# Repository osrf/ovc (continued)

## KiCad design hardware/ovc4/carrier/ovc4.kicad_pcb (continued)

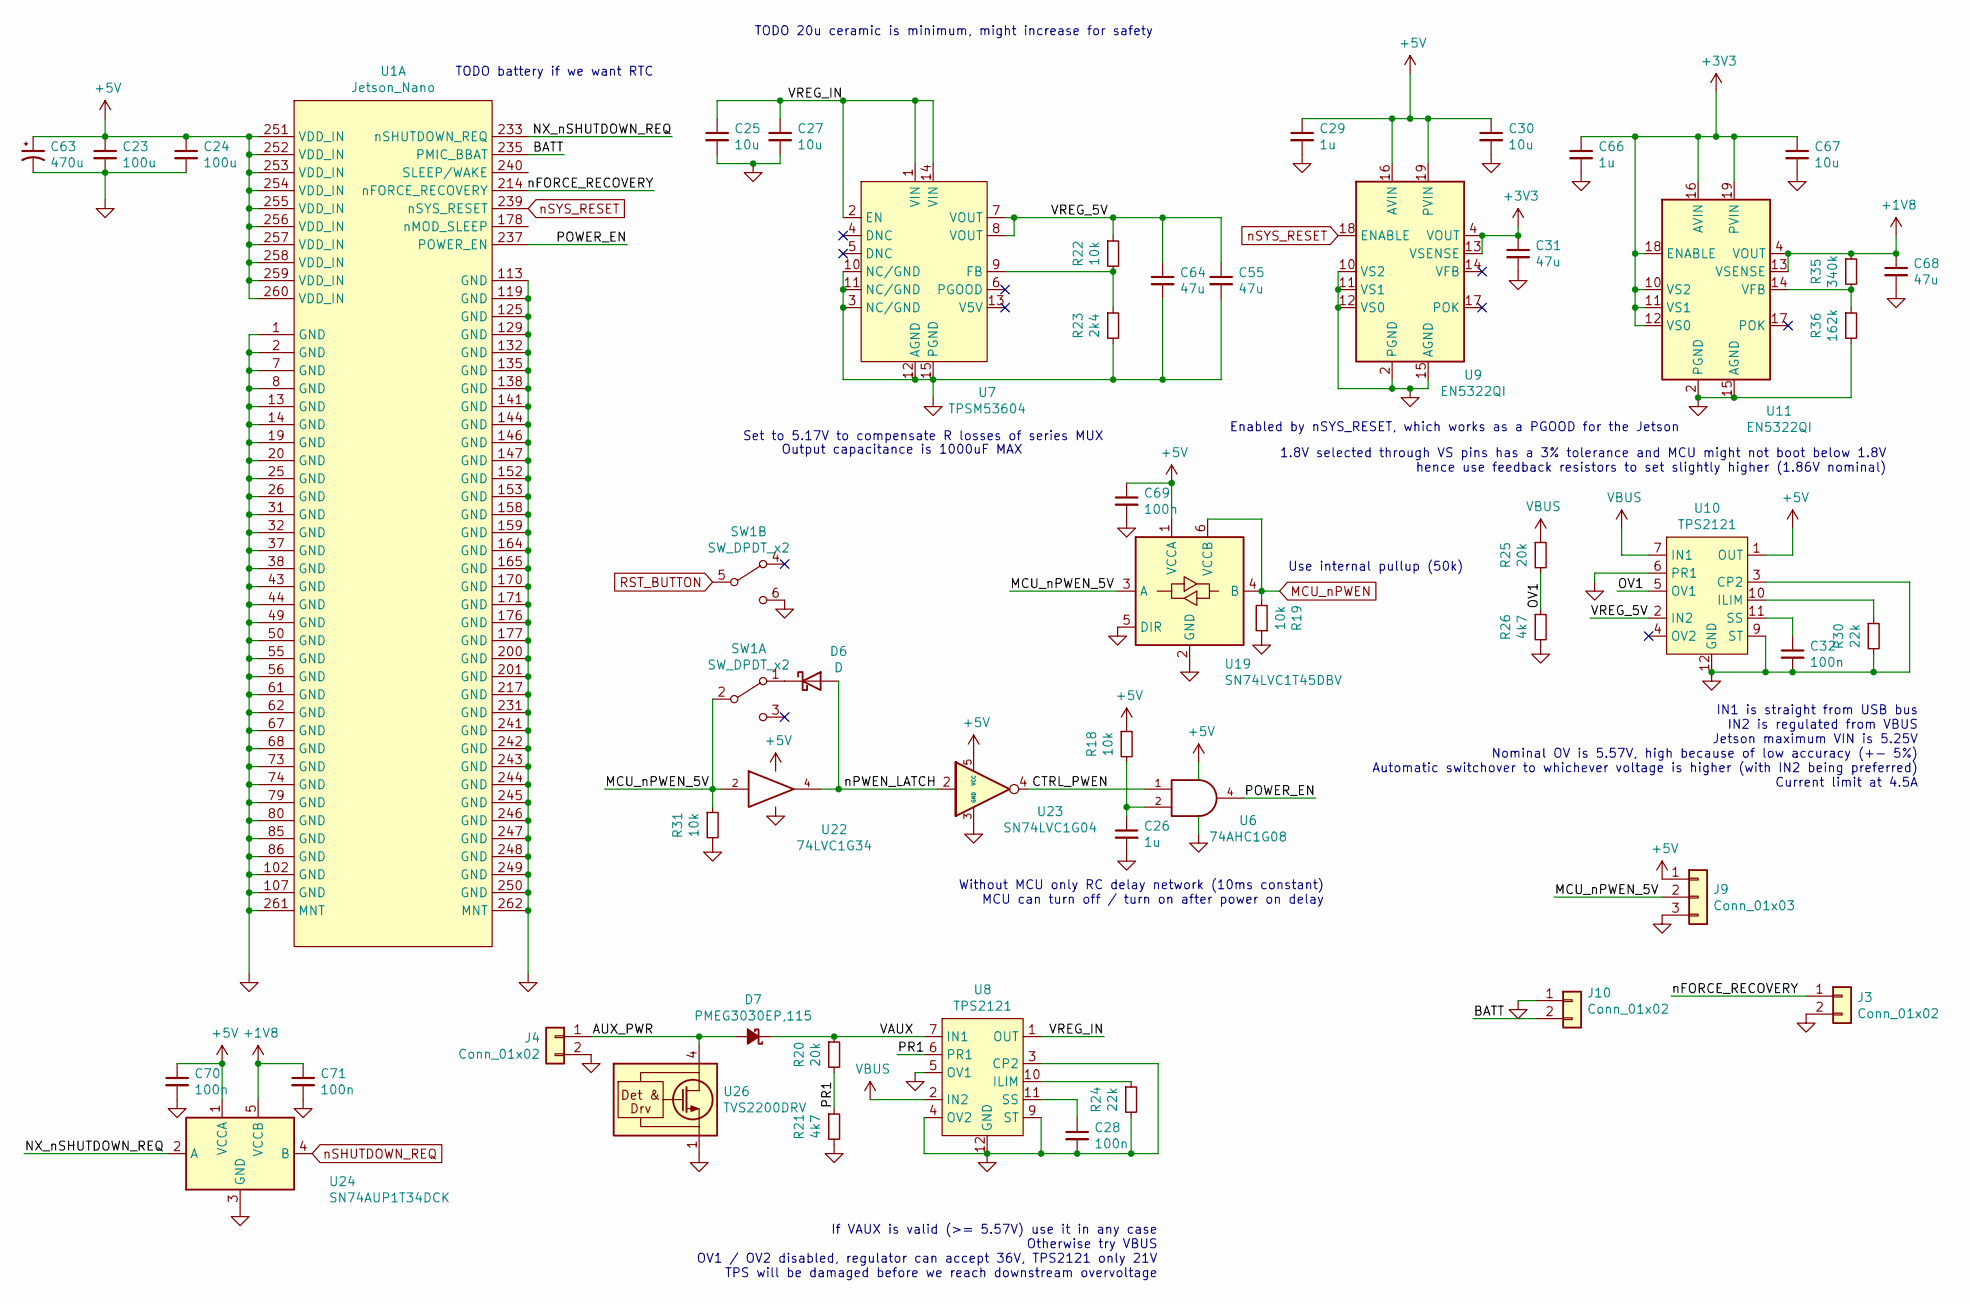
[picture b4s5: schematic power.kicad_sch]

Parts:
C23, C24: 100u; C_1206_3216Metric; MPN C3216X5R1A107M160AC
C25, C27: 10u; C_1206_3216Metric; MPN C1206C106M3PACTU
C26, C29, C66: 1u; C_0402_1005Metric; MPN CL05A105KA5NQNC
C28, C32, C69, C70, C71: 100n; C_0402_1005Metric; MPN CL05F104ZO5NNNC
C30, C67: 10u; C_0805_2012Metric; MPN C0805C106K8PACTU
C31, C55, C64, C68: 47u; C_1206_3216Metric; MPN GRM31CR61A476KE15L
C63: 470u; CP_Elec_6.3x7.7; MPN EEE-FTJ471XAP
D6: D; D_0402_1005Metric; MPN CDBQR0130L
D7: PMEG3030EP,115; D_SOD-128; MPN PMEG3030EP,115
J3: Conn_01x02; PinHeader_1x02_P2.54mm_Vertical; MPN 952-2262-ND
J4: Conn_01x02; Molex_Nano-Fit_105313-xx02_1x02_P2.50mm_Horizontal; MPN 1053131302
J9: Conn_01x03; PinHeader_1x03_P2.54mm_Vertical; MPN CONN HEADER VERT 3POS 2.54MM
J10: Conn_01x02; ELNA_DSK-3R3H224U-HL; MPN DSK-3R3H224U-HL
R18, R19, R22, R31: 10k; R_0402_1005Metric; MPN ERA-2AED103X
R20, R25: 20k; R_0402_1005Metric; MPN ERA-2AED103X
R21, R26: 4k7; R_0402_1005Metric; MPN ERJ-2RKF4701X
R23: 2k4; R_0402_1005Metric; MPN ERA-2AED242X
R24, R30: 22k; R_0402_1005Metric; MPN ERJ-2RKF2202X
R35: 340k; R_0402_1005Metric; MPN ERJ-2RKF3403X
R36: 162k; R_0402_1005Metric; MPN ERJ-2RKF1623X
SW1: SW_DPDT_x2; TL2230; MPN TL2230OAF140
U1: Jetson_Nano; TE_2309413-1; MPN 2309413-1
U6: 74AHC1G08; SOT-353_SC-70-5; MPN SN74AHC1G08DCKR
U7: TPSM53604; TI_B3QFN; MPN TPSM53604RDAR
U8, U10: TPS2121; Texas_VQFN-HR-12_2x2.5_Pitch0.5mm; MPN TPS2121RUXR
U9, U11: EN5322QI; Converter_DCDC_Intel_QFN-24_4x6mm_P0.65mm_ThermalVias; MPN EN5322QI
U19: SN74LVC1T45DBV; SOT-23-6; MPN SN74LVC1T45DBVR
U22: 74LVC1G34; SOT-23-5; MPN SN74LVC1G34DBVR
U23: SN74LVC1G04; SOT-353_SC-70-5; MPN SN74LVC1G04DCKR
U24: SN74AUP1T34DCK; SOT-353_SC-70-5; MPN SN74AUP1T34DCKR
U26: TVS2200DRV; WSON-6-1EP_2x2mm_P0.65mm_EP1x1.6mm; MPN TVS2200DRVR

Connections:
+1V8: C68.1, C71.1, R35.1, U11.4 (VOUT), U11.5 (VOUT), U11.6 (VOUT), U11.7 (VOUT), U11.13 (VSENSE), U24.5 (VCCB); also elsewhere on the board
+5V: C23.1, C24.1, C29.1, C30.1, C63.1, C69.1, C70.1, J9.1, R18.1, U1.251 (VDD_IN), U1.252 (VDD_IN), U1.253 (VDD_IN), U1.254 (VDD_IN), U1.255 (VDD_IN), U1.256 (VDD_IN), U1.257 (VDD_IN), U1.258 (VDD_IN), U1.259 (VDD_IN), U1.260 (VDD_IN), U6.5 (VCC), U9.16 (AVIN), U9.19 (PVIN), U9.20 (PVIN), U10.1 (OUT), U10.8 (OUT), U19.1 (VCCA), U22.5 (VCC), U23.5 (VCC), U24.1 (VCCA); also elsewhere on the board
/Power/AUX_PWR: D7.2 (A), J4.1, U26.4 (IN), U26.5 (IN), U26.6 (IN)
/Power/BATT: J10.2, U1.235 (PMIC_BBAT)
/Power/CTRL_PWEN: U6.1, U23.4
/Power/MCU_nPWEN_5V: J9.2, R31.1, SW1.2 (B), U19.3 (A), U22.2
/Power/NX_nSHUTDOWN_REQ: U1.233 (nSHUTDOWN_REQ), U24.2 (A)
/Power/OV1: R25.2, R26.1, U10.5 (OV1)
/Power/POWER_EN: U1.237 (POWER_EN), U6.4
/Power/PR1: R20.2, R21.1, U8.6 (PR1)
/Power/VAUX: D7.1 (K), R20.1, U8.7 (IN1)
/Power/VREG_5V: C55.1, C64.1, R22.1, U7.7 (VOUT), U7.8 (VOUT), U10.2 (IN2)
/Power/VREG_IN: C25.1, C27.1, U7.1 (VIN), U7.2 (EN), U7.14 (VIN), U8.1 (OUT), U8.8 (OUT)
/Power/nFORCE_RECOVERY: J3.1, U1.214 (nFORCE_RECOVERY)
/Power/nPWEN_LATCH: D6.2 (A), U22.4, U23.2
GND: C23.2, C24.2, C25.2, C26.2, C27.2, C28.2, C29.2, C30.2, C31.2, C32.2, C55.2, C63.2, C64.2, C66.2, C67.2, C68.2, C69.2, C70.2, C71.2, J3.2, J4.2, J9.3, J10.1, R19.1, R21.2, R23.2, R24.2, R26.2, R30.2, R31.2, R36.2, SW1.6 (C), U1.1 (GND), U1.2 (GND), U1.7 (GND), U1.8 (GND), U1.13 (GND), U1.14 (GND), U1.19 (GND), U1.20 (GND), U1.25 (GND), U1.26 (GND), U1.31 (GND), U1.32 (GND), U1.37 (GND), U1.38 (GND), U1.43 (GND), U1.44 (GND), U1.49 (GND), U1.50 (GND), U1.55 (GND), U1.56 (GND), U1.61 (GND), U1.62 (GND), U1.67 (GND), U1.68 (GND), U1.73 (GND), U1.74 (GND), U1.79 (GND), U1.80 (GND), U1.85 (GND), U1.86 (GND), U1.102 (GND), U1.107 (GND), U1.113 (GND), U1.119 (GND), U1.125 (GND), U1.129 (GND), U1.132 (GND), U1.135 (GND), U1.138 (GND), U1.141 (GND), U1.144 (GND), U1.146 (GND), U1.147 (GND), U1.152 (GND), U1.153 (GND), U1.158 (GND), U1.159 (GND), U1.164 (GND), U1.165 (GND), U1.170 (GND), U1.171 (GND), U1.176 (GND), U1.177 (GND), U1.200 (GND), U1.201 (GND), U1.217 (GND), U1.231 (GND), U1.241 (GND), U1.242 (GND), U1.243 (GND), U1.244 (GND), U1.245 (GND), U1.246 (GND), U1.247 (GND), U1.248 (GND), U1.249 (GND), U1.250 (GND), U1.261 (MNT), U1.262 (MNT), U6.3 (GND), U7.3 (NC/GND), U7.10 (NC/GND), U7.11 (NC/GND), U7.12 (AGND), U7.15 (PGND), U8.3 (CP2), U8.4 (OV2), U8.5 (OV1), U8.9 (ST), U8.12 (GND), U9.2 (PGND), U9.3 (PGND), U9.8 (PGND), U9.9 (PGND), U9.10 (VS2), U9.11 (VS1), U9.12 (VS0), U9.15 (AGND), U9.25 (PGND), U10.3 (CP2), U10.6 (PR1), U10.9 (ST), U10.12 (GND), U11.2 (PGND), U11.3 (PGND), U11.8 (PGND), U11.9 (PGND), U11.15 (AGND), U11.25 (PGND), U19.2 (GND), U19.5 (DIR), U22.3 (GND), U23.3 (GND), U24.3 (GND), U26.1 (GND), U26.2 (GND), U26.3 (GND), U26.7 (GND); also elsewhere on the board
MCU_nPWEN: R19.2, U19.4 (B), U19.6 (VCCB); also elsewhere on the board
unnamed: C26.1, R18.2, U6.2
unnamed: C28.1, U8.11 (SS)
unnamed: C32.1, U10.11 (SS)
unnamed: D6.1 (K), SW1.1 (A)
unnamed: R22.2, R23.1, U7.9 (FB)
unnamed: R24.1, U8.10 (ILIM)
unnamed: R30.1, U10.10 (ILIM)
unnamed: R35.2, R36.1, U11.14 (VFB)
RST_BUTTON: SW1.5 (B); also elsewhere on the board
VBUS: R25.1, U8.2 (IN2), U10.7 (IN1); also elsewhere on the board
nSHUTDOWN_REQ: U24.4 (B); also elsewhere on the board
nSYS_RESET: U1.239 (nSYS_RESET), U9.18 (ENABLE); also elsewhere on the board

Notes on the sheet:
TODO battery if we want RTC
Output capacitance is 1000uF MAX
Set to 5.17V to compensate R losses of series MUX
TODO 20u ceramic is minimum, might increase for safety
If VAUX is valid (>= 5.57V) use it in any case Otherwise try VBUS OV1 / OV2 disabled, regulator can accept 36V, TPS2121 only 21V TPS will be damaged before we reach downstream overvoltage
Without MCU only RC delay network (10ms constant) MCU can turn off / turn on after power on delay
Use internal pullup (50k)
Enabled by nSYS_RESET, which works as a PGOOD for the Jetson
1.8V selected through VS pins has a 3% tolerance and MCU might not boot below 1.8V hence use feedback resistors to set slightly higher (1.86V nominal)
IN1 is straight from USB bus IN2 is regulated from VBUS Jetson maximum VIN is 5.25V Nominal OV is 5.57V, high because of low accuracy (+- 5%) Automatic switchover to whichever voltage is higher (with IN2 being preferred) Current limit at 4.5A

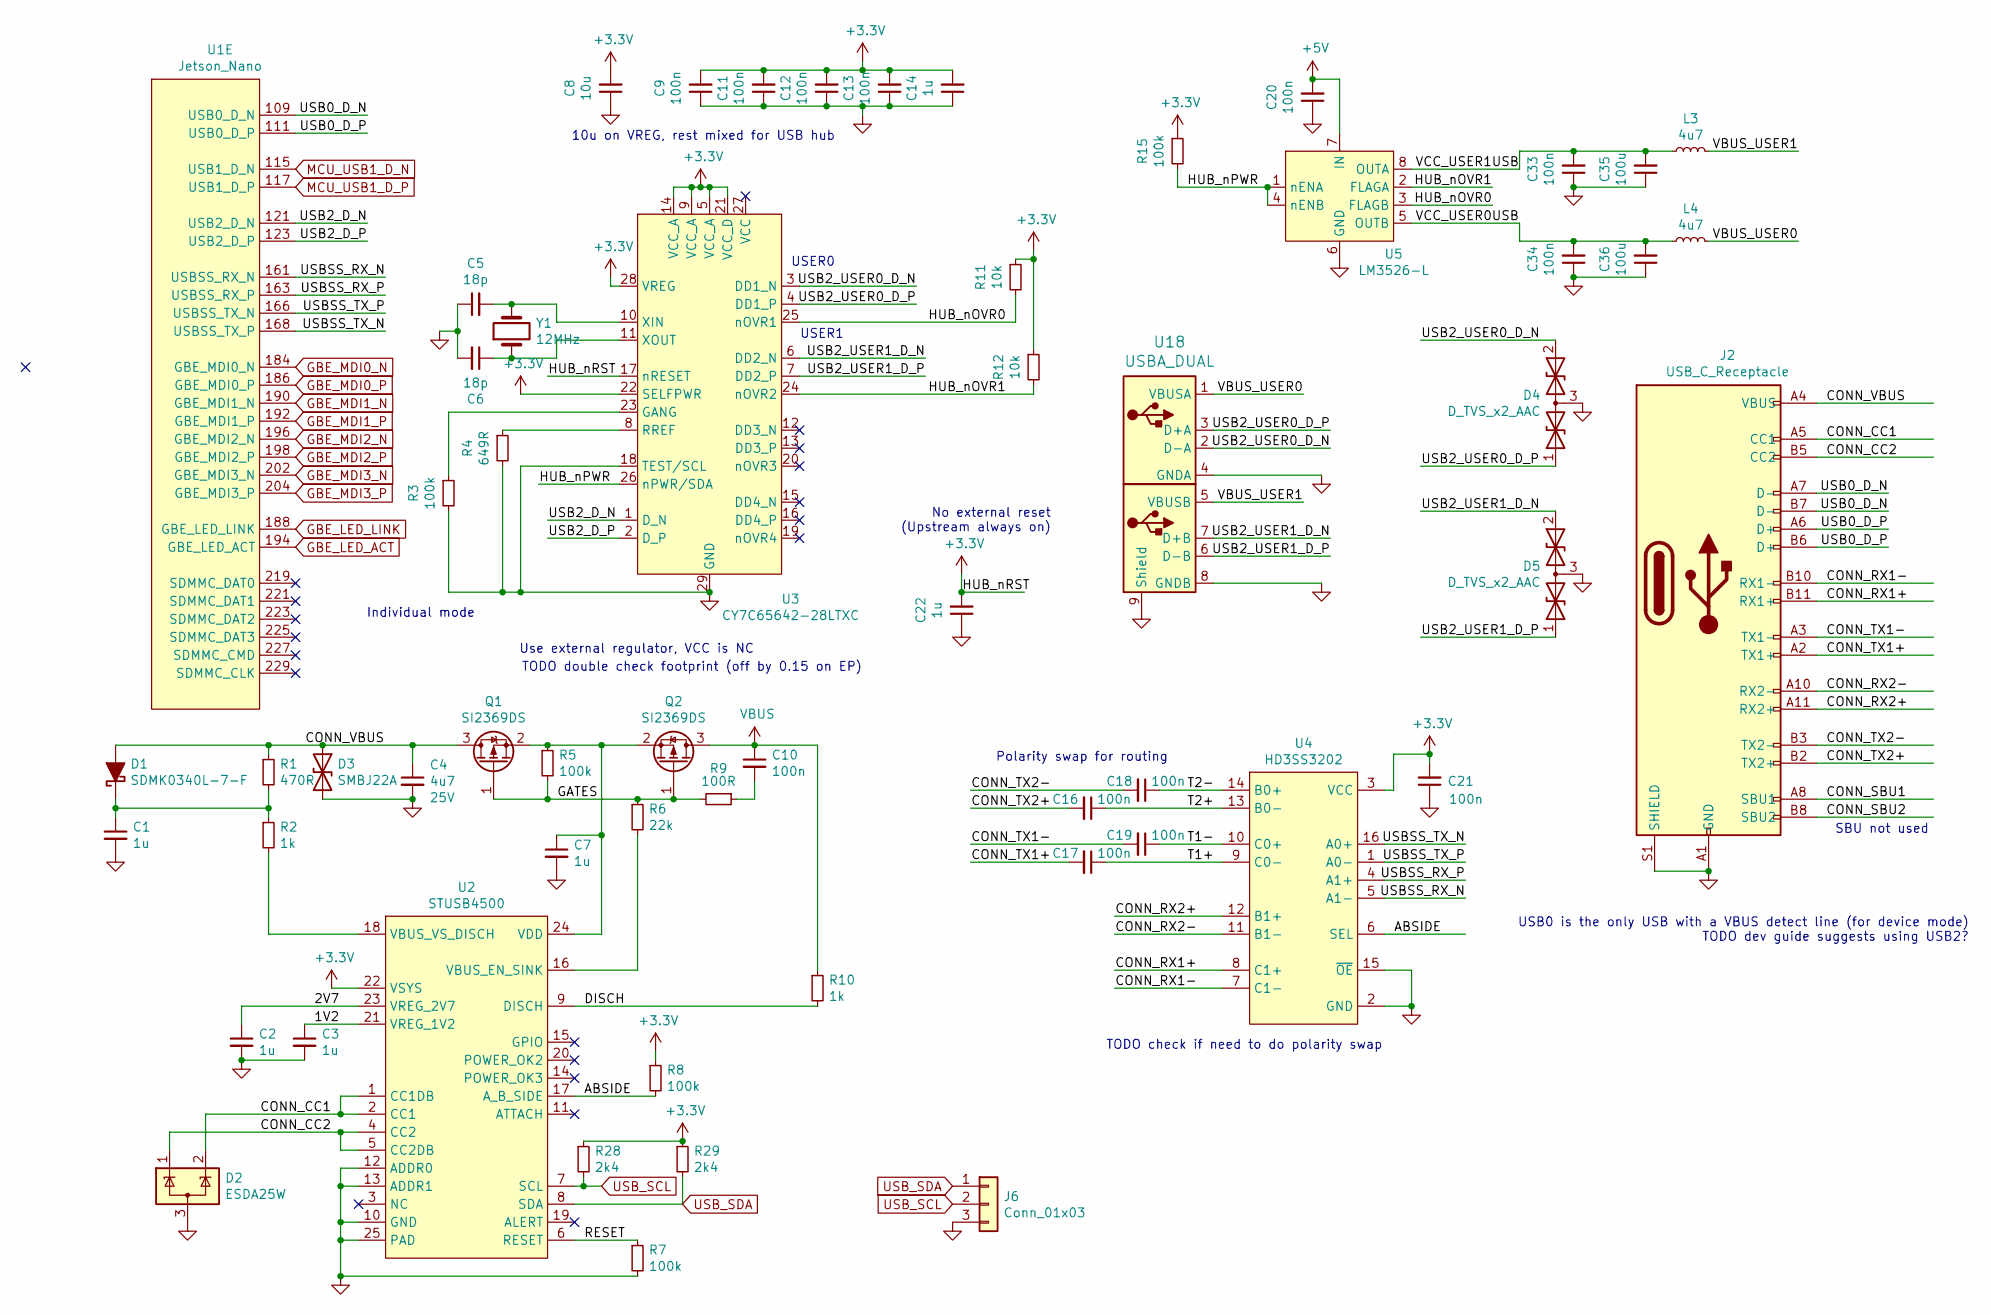
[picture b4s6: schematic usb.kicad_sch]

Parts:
C1, C2, C3, C7, C14, C22: 1u; C_0402_1005Metric; MPN CL05A105KA5NQNC
C4: 4u7; C_0603_1608Metric; voltage 25V; MPN CL10A475KA8NQNC
C5, C6: 18p; C_0402_1005Metric; MPN CC0402JRNPO9BN180
C8: 10u; C_0402_1005Metric; MPN GRM155C80J106ME11J
C9, C10, C11, C12, C13, C16, C17, C18, C19, C20, C21, C33, C34: 100n; C_0402_1005Metric; MPN CL05F104ZO5NNNC
C35, C36: 100u; C_1206_3216Metric; MPN GRM31CD80J107ME39L
D1: SDMK0340L-7-F; D_SOD-323; MPN SDMK0340L-7-F
D2: ESDA25W; SOT-23; MPN ESDA25W
D3: SMBJ22A; D_SMB; MPN SMBJ22A
D4, D5: D_TVS_x2_AAC; TPD2EUSB30x; MPN TPD2EUSB30DRTR
J2: USB_C_Receptacle; USB_C_Receptacle_Wurth_632723300011; MPN 632723300011
J6: Conn_01x03; PinHeader_1x03_P2.54mm_Vertical; MPN CONN HEADER VERT 3POS 2.54MM
L3, L4: 4u7; L_0805_2012Metric; MPN LQM2MPN4R7MG0L
Q1, Q2: SI2369DS; SOT-23; MPN SI2369DS-T1-GE3
R1: 470R; R_0402_1005Metric; MPN ERJ-2RKF4700X
R2: 1k; R_0402_1005Metric; MPN ERJ-2RKF1001X
R3, R5, R7, R8, R15: 100k; R_0402_1005Metric; MPN ERA-2AED104X
R4: 649R; R_0402_1005Metric; MPN ERA-2AEB6490X
R6: 22k; R_0402_1005Metric; MPN ERJ-2RKF2202X
R9: 100R; R_0402_1005Metric; MPN ERA-2AED101X
R10: 1k; R_0603_1608Metric; MPN ESR03EZPJ102
R11, R12: 10k; R_0402_1005Metric; MPN ERA-2AED103X
R28, R29: 2k4; R_0402_1005Metric; MPN ERA-2AED242X
U1: Jetson_Nano; TE_2309413-1; MPN 2309413-1
U2: STUSB4500; QFN-24-1EP_4x4mm_P0.5mm_EP2.7x2.7mm; MPN STUSB4500LQTR
U3: CY7C65642-28LTXC; QFN-28-1EP_5x5mm_P0.5mm_EP3.35x3.35mm; MPN CY7C65642-28LTXC
U4: HD3SS3202; TI_R_PUQFN_N16; MPN HD3SS3202IRSVT
U5: LM3526-L; SO-8_3.9x4.9mm_P1.27mm; MPN LM3526MX-L/NOPB
U18: USBA_DUAL; USBA_DUAL_HOR; MPN 72309-8034BLF
Y1: 12MHz; Crystal_SMD_5032-2Pin_5.0x3.2mm; MPN CX5032GB12000H0HPQZ1

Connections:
+5V: C20.2, U5.7 (IN); also elsewhere on the board
/USB/1V2: C3.1, U2.21 (VREG_1V2)
/USB/2V7: C2.1, U2.23 (VREG_2V7)
/USB/ABSIDE: R8.2, U2.17 (A_B_SIDE), U4.6 (SEL)
/USB/CONN_CC1: D2.2 (K), J2.A5 (CC1), U2.1 (CC1DB), U2.2 (CC1)
/USB/CONN_CC2: D2.1 (K), J2.B5 (CC2), U2.4 (CC2), U2.5 (CC2DB)
/USB/CONN_RX1+: J2.B11 (RX1+), U4.8 (C1+)
/USB/CONN_RX1-: J2.B10 (RX1-), U4.7 (C1-)
/USB/CONN_RX2+: J2.A11 (RX2+), U4.12 (B1+)
/USB/CONN_RX2-: J2.A10 (RX2-), U4.11 (B1-)
/USB/CONN_SBU1: J2.A8 (SBU1)
/USB/CONN_SBU2: J2.B8 (SBU2)
/USB/CONN_TX1+: C17.2, J2.A2 (TX1+)
/USB/CONN_TX1-: C19.2, J2.A3 (TX1-)
/USB/CONN_TX2+: C16.2, J2.B2 (TX2+)
/USB/CONN_TX2-: C18.2, J2.B3 (TX2-)
/USB/CONN_VBUS: C4.1, D1.2 (A), D3.1 (A1), J2.A4 (VBUS), J2.A9 (VBUS), J2.B4 (VBUS), J2.B9 (VBUS), Q1.3 (D), R1.1
/USB/DISCH: R10.2, U2.9 (DISCH)
/USB/GATES: Q1.1 (G), Q2.1 (G), R5.2, R6.1, R9.2
/USB/HUB_nOVR0: R11.2, U3.25 (nOVR1), U5.3 (FLAGB)
/USB/HUB_nOVR1: R12.2, U3.24 (nOVR2), U5.2 (FLAGA)
/USB/HUB_nPWR: R15.2, U3.26 (nPWR/SDA), U5.1 (nENA), U5.4 (nENB)
/USB/RESET: R7.1, U2.6 (RESET)
/USB/T1+: C17.1, U4.9 (C0-)
/USB/T1-: C19.1, U4.10 (C0+)
/USB/T2+: C16.1, U4.13 (B0-)
/USB/T2-: C18.1, U4.14 (B0+)
/USB/USB0_D_N: J2.A7 (D-), J2.B7 (D-), U1.109 (USB0_D_N)
/USB/USB0_D_P: J2.A6 (D+), J2.B6 (D+), U1.111 (USB0_D_P)
/USB/USB2_D_N: U1.121 (USB2_D_N), U3.1 (D_N)
/USB/USB2_D_P: U1.123 (USB2_D_P), U3.2 (D_P)
/USB/USB2_USER0_D_N: D4.2 (A2), U3.3 (DD1_N), U18.2 (D-A)
/USB/USB2_USER0_D_P: D4.1 (A1), U3.4 (DD1_P), U18.3 (D+A)
/USB/USB2_USER1_D_N: D5.2 (A2), U3.6 (DD2_N), U18.7 (D+B)
/USB/USB2_USER1_D_P: D5.1 (A1), U3.7 (DD2_P), U18.6 (D-B)
/USB/USBSS_RX_N: U1.161 (USBSS_RX_N), U4.5 (A1-)
/USB/USBSS_RX_P: U1.163 (USBSS_RX_P), U4.4 (A1+)
/USB/USBSS_TX_N: U1.168 (USBSS_TX_P), U4.16 (A0+)
/USB/USBSS_TX_P: U1.166 (USBSS_TX_N), U4.1 (A0-)
/USB/VBUS_USER0: L4.2, U18.1 (VBUSA)
/USB/VBUS_USER1: L3.2, U18.5 (VBUSB)
/USB/VCC_USER0USB: C34.2, C36.2, L4.1, U5.5 (OUTB)
/USB/VCC_USER1USB: C33.2, C35.2, L3.1, U5.8 (OUTA)
GBE_LED_ACT: U1.194 (GBE_LED_ACT); also elsewhere on the board
GBE_LED_LINK: U1.188 (GBE_LED_LINK); also elsewhere on the board
GBE_MDI0_N: U1.184 (GBE_MDI0_N); also elsewhere on the board
GBE_MDI0_P: U1.186 (GBE_MDI0_P); also elsewhere on the board
GBE_MDI1_N: U1.190 (GBE_MDI1_N); also elsewhere on the board
GBE_MDI1_P: U1.192 (GBE_MDI1_P); also elsewhere on the board
GBE_MDI2_N: U1.196 (GBE_MDI2_N); also elsewhere on the board
GBE_MDI2_P: U1.198 (GBE_MDI2_P); also elsewhere on the board
GBE_MDI3_N: U1.202 (GBE_MDI3_N); also elsewhere on the board
GBE_MDI3_P: U1.204 (GBE_MDI3_P); also elsewhere on the board
GND: C1.2, C2.2, C3.2, C4.2, C5.1, C6.2, C7.2, C8.1, C9.1, C11.1, C12.1, C13.1, C14.1, C20.1, C21.1, C22.1, C33.1, C34.1, C35.1, C36.1, D2.3 (A), D3.2 (A2), D4.3 (common), D5.3 (common), J2.A1 (GND), J2.A12 (GND), J2.B1 (GND), J2.B12 (GND), J2.S1 (SHIELD), J6.3, R3.2, R4.2, R7.2, U2.10 (GND), U2.12 (ADDR0), U2.13 (ADDR1), U2.25 (PAD), U3.18 (TEST/SCL), U3.29 (GND), U4.2 (GND), U4.15 (~OE), U5.6 (GND), U18.4 (GNDA), U18.8 (GNDB), U18.9 (Shield); also elsewhere on the board
MCU_USB1_D_N: U1.115 (USB1_D_N); also elsewhere on the board
MCU_USB1_D_P: U1.117 (USB1_D_P); also elsewhere on the board
unnamed: C1.1, D1.1 (K), R1.2, R2.1
unnamed: C5.2, U3.10 (XIN), Y1.2
unnamed: C6.1, U3.11 (XOUT), Y1.1
unnamed: C7.1, Q1.2 (S), Q2.2 (S), R5.1, U2.24 (VDD)
unnamed: C10.2, R9.1
unnamed: R2.2, U2.18 (VBUS_VS_DISCH)
unnamed: R3.1, U3.23 (GANG)
unnamed: R4.1, U3.8 (RREF)
unnamed: R6.2, U2.16 (VBUS_EN_SINK)
USB_SCL: J6.2, R28.2, U2.7 (SCL)
USB_SDA: J6.1, R29.2, U2.8 (SDA)
VBUS: C10.1, Q2.3 (D), R10.1; also elsewhere on the board

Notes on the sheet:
Individual mode
Use external regulator, VCC is NC
10u on VREG, rest mixed for USB hub
USER0
USER1
TODO double check footprint (off by 0.15 on EP)
No external reset (Upstream always on)
TODO check if need to do polarity swap
Polarity swap for routing
SBU not used
USB0 is the only USB with a VBUS detect line (for device mode) TODO dev guide suggests using USB2?

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
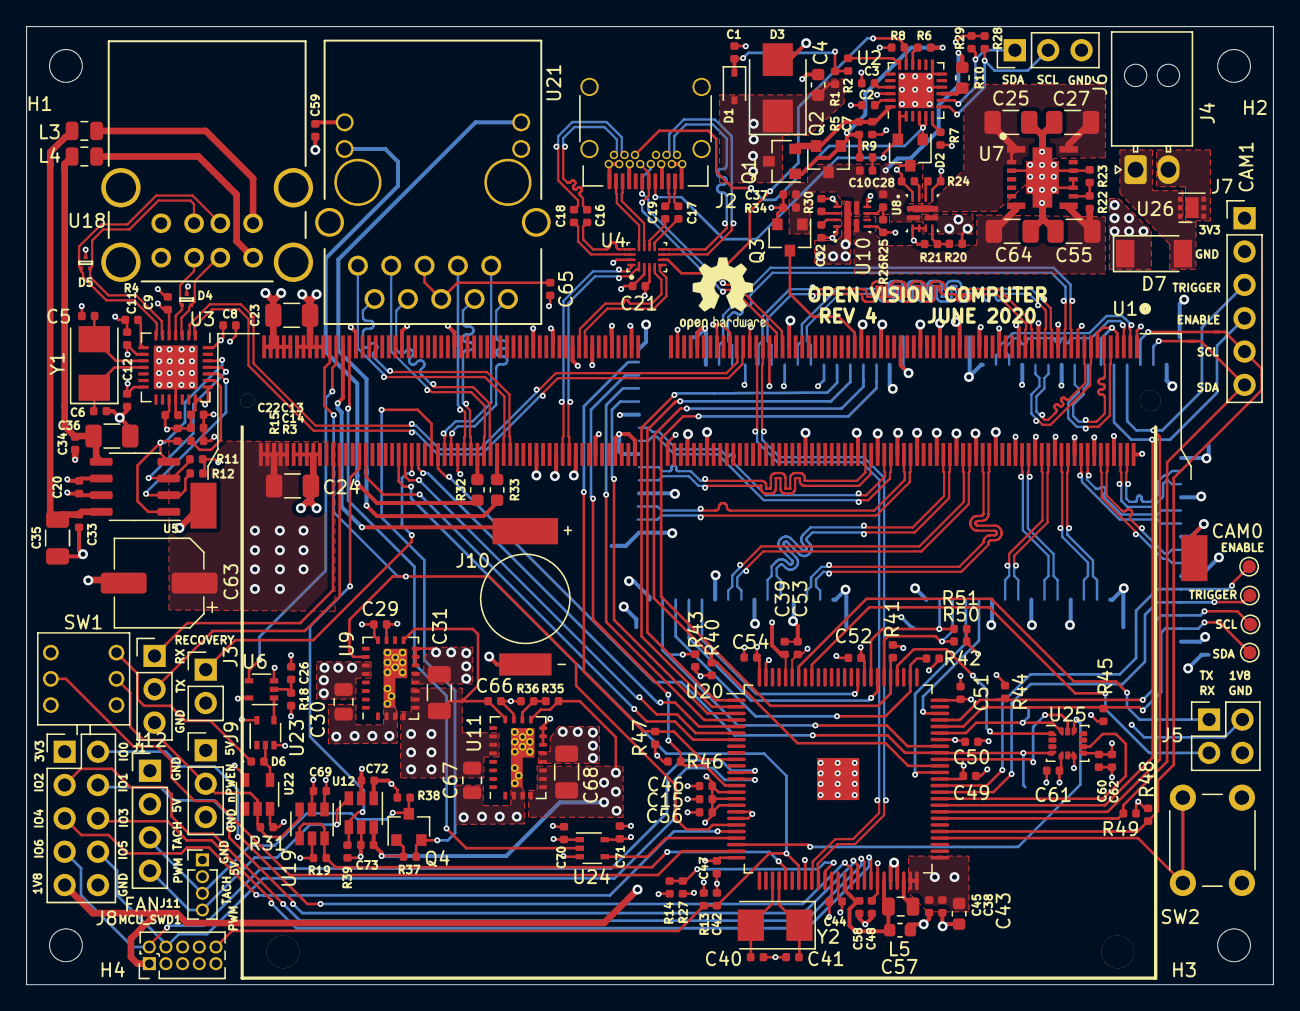
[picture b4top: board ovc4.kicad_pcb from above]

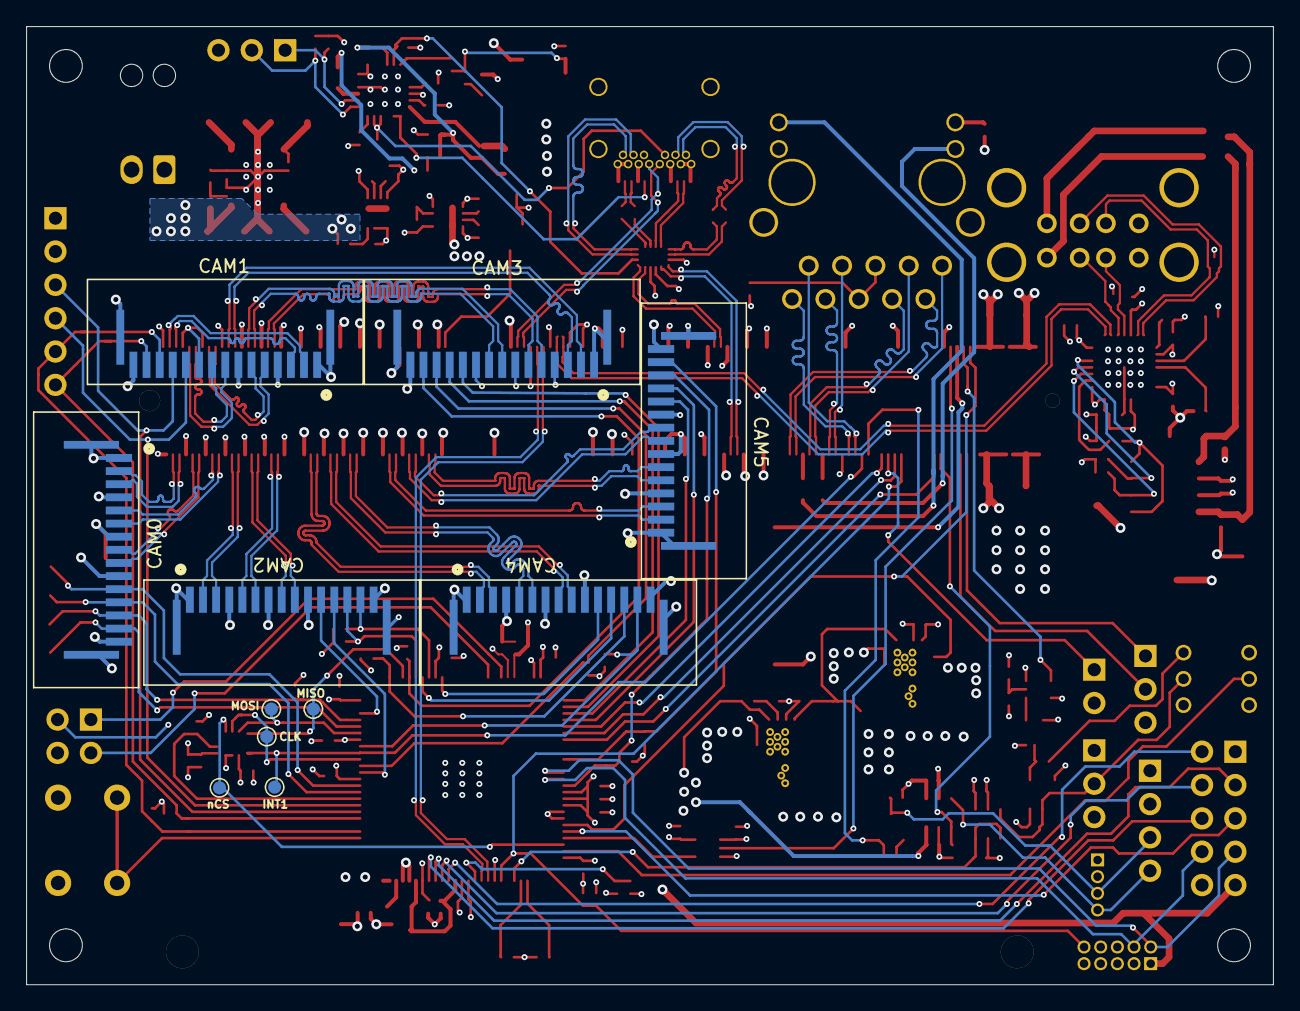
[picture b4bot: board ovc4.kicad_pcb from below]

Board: 6 copper layers, 95.0 x 73.0 mm, 194 parts (11 on the bottom side), 188 nets.

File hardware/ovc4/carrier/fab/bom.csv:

Component,Quantity Per PCB,References,Value,Footprint,MFN,MPN,D1N,D1PN,voltage
1,41,C9 C10 C11 C12 C13 C15 C16 C17 C18 C19 C20 C21 C28 C32 C33 C34 C37 C38 C39 C42 C44 C46 C47 C48 C49 C50 C51 C52 C53 C54 C56 C58 C59 C60 C61 C65 C69 C70 C71 C72 C73,100n,C_0402_1005Metric,Samsung,CL05F104ZO5NNNC,Digikey,1276-1004-1-ND,
2,4,C23 C24 C35 C36,100u,C_1206_3216Metric,TDK,C3216X5R1A107M160AC,Digikey,445-6007-1-ND,
3,2,C25 C27,10u,C_1206_3216Metric,KEMET,C1206C106M3PACTU,Digikey,399-8153-1-ND,
4,2,C30 C67,10u,C_0805_2012Metric,Kemet,C0805C106K8PACTU,Digikey,399-4925-1-ND,
5,2,C43 C57,10u,C_0603_1608Metric,Murata,GRM188R61A106KE69J,Digikey,490-14372-1-ND,
6,1,C8,10u,C_0402_1005Metric,Murata,GRM155C80J106ME11J,Digikey,490-18210-1-ND,
7,4,C5 C6 C40 C41,18p,C_0402_1005Metric,Yageo,CC0402JRNPO9BN180,Digikey,311-1415-1-ND,
8,9,C1 C2 C3 C7 C14 C22 C26 C29 C66,1u,C_0402_1005Metric,Samsung,CL05A105KA5NQNC,Digikey,1276-1445-1-ND,
9,1,C62,2u2,C_0402_1005Metric,Murata,GRM155R61A225KE95D,Digikey,490-10451-1-ND,
10,1,C63,470u,CP_Elec_6.3x7.7,Panasonic,EEE-FTJ471XAP,Digikey,P15096CT-ND,
11,1,C45,47p,C_0402_1005Metric,Kemet,C0402C470K5GACTU,Digikey,399-7796-1-ND,
12,4,C31 C55 C64 C68,47u,C_1206_3216Metric,Murata,GRM31CR61A476KE15L,Digikey,490-9673-1-ND,
13,1,C4,4u7,C_0603_1608Metric,Samsung,CL10A475KA8NQNC,Digikey,1276-1900-1-ND,25V
14,6,CAM0 CAM1 CAM2 CAM3 CAM4 CAM5,PICAM,AMPHENOL_SFW15R,Amphenol,SFW15R-1STE1LF,Digikey,609-1905-1-ND,
15,1,D6,D,D_0402_1005Metric,Comchip,CDBQR0130L,Digikey,641-1271-1-ND,
16,2,D4 D5,D_TVS_x2_AAC,TPD2EUSB30x,TI,TPD2EUSB30DRTR,Digikey,296-25509-1-ND,
17,1,D2,ESDA25W,SOT-23,ST,ESDA25W,Digikey,497-6689-1-ND,
18,1,D7,"PMEG3030EP,115",D_SOD-128,Nexperia,"PMEG3030EP,115",Digikey,1727-5324-1-ND,
19,1,D1,SDMK0340L-7-F,D_SOD-323,Diodes Inc,SDMK0340L-7-F,Digikey,SDMK0340L-FDICT-ND,
20,1,D3,SMBJ22A,D_SMB,Bourns,SMBJ22A,Digikey,SMBJ22ABCT-ND,
21,1,J10,Conn_01x02,ELNA_DSK-3R3H224U-HL,Elna,DSK-3R3H224U-HL,Digikey,604-1020-1-ND,
22,1,J3,Conn_01x02,PinHeader_1x02_P2.54mm_Vertical,Harwin,952-2262-ND,Digikey,952-2262-ND,
23,1,J4,Conn_01x02,Molex_Nano-Fit_105313-xx02_1x02_P2.50mm_Horizontal,Molex,1053131302,Digikey,WM15141-ND,
24,3,J1 J6 J9,Conn_01x03,PinHeader_1x03_P2.54mm_Vertical,Wurth,CONN HEADER VERT 3POS 2.54MM,Digikey,732-5316-ND,
25,1,J11,Conn_01x04,PinHeader_1x04_P1.27mm_Vertical,Adam Tech,HPH1-B-04-UA,Digikey,2057-HPH1-B-04-UA-ND,
26,1,J12,Conn_01x04,PinHeader_1x04_P2.54mm_Vertical,Wurth,61300411121,Digikey,732-5317-ND,
27,1,J7,Conn_01x06,PinHeader_1x06_P2.54mm_Vertical,Amphenol,68000-406HLF,Digikey,609-3263-ND,
28,1,J8,Conn_02x05_Odd_Even,PinHeader_2x05_P2.54mm_Vertical,Sullins,PPTC052LFBN-RC,Digikey,S6105-ND,
29,1,J5,ISP_UART,PinHeader_2x02_P2.54mm_Vertical,Harwin,M20-9760246,Digikey,952-1772-ND,
30,1,J2,USB_C_Receptacle,USB_C_Receptacle_Wurth_632723300011,Wurth,632723300011,Digikey,732-9618-1-ND,
31,3,L3 L4 L5,4u7,L_0805_2012Metric,Murata,LQM2MPN4R7MG0L,Digikey,490-12073-1-ND,
32,1,LOGO1,Logo_Open_Hardware_Large,OSHW-Logo2_7.3x6mm_SilkScreen,,,,,
33,1,MCU_SWD1,Conn_ARM_JTAG_SWD_10,PinHeader_2x05_P1.27mm_Vertical,Amphenol,20021111-00010T4LF,Digikey,609-3712-ND,
34,2,Q3 Q4,2N7002,SOT-23,Nexperia,"2N7002,215",Digikey,1727-2764-1-ND,
35,2,Q1 Q2,SI2369DS,SOT-23,Vishay,SI2369DS-T1-GE3,Digikey,SI2369DS-T1-GE3CT-ND,
36,1,R9,100R,R_0402_1005Metric,Panasonic,ERA-2AED101X,Digikey,P100DECT-ND,
37,7,R3 R5 R7 R8 R13 R15 R39,100k,R_0402_1005Metric,Panasonic,ERA-2AED104X,Digikey,P100KDECT-ND,
38,9,R11 R12 R14 R18 R19 R22 R31 R37 R38,10k,R_0402_1005Metric,Panasonic,ERA-2AED103X,Digikey,P10KDECT-ND,
39,2,R32 R33,110R,R_0603_1608Metric,Panasonic,ERA-3AEB111V,Digikey,P110DBCT-ND,
40,1,R36,162k,R_0402_1005Metric,Panasonic,ERJ-2RKF1623X,Digikey,P162KLCT-ND,
41,1,R34,1M,R_0402_1005Metric,Yageo,RC0402FR-071ML,Digikey,311-1.00MLRCT-ND,
42,1,R10,1k,R_0603_1608Metric,Rohm,ESR03EZPJ102,Digikey,RHM1.0KDCT-ND,
43,1,R2,1k,R_0402_1005Metric,Panasonic,ERJ-2RKF1001X,Digikey,P1.00KLCT-ND,
44,3,R20 R25 R27,20k,R_0402_1005Metric,Panasonic,ERA-2AED103X,Digikey,P10KDECT-ND,
45,3,R6 R24 R30,22k,R_0402_1005Metric,Panasonic,ERJ-2RKF2202X,Digikey,P22.0KLCT-ND,
46,15,R23 R28 R29 R40 R41 R42 R43 R44 R45 R46 R47 R48 R49 R50 R51,2k4,R_0402_1005Metric,Panasonic,ERA-2AED242X,Digikey,P2.4KDECT-ND,
47,1,R35,340k,R_0402_1005Metric,Panasonic,ERJ-2RKF3403X,Digikey,P340KLCT-ND,
48,1,R1,470R,R_0402_1005Metric,Panasonic,ERJ-2RKF4700X,Digikey,P470LCT-ND,
49,2,R21 R26,4k7,R_0402_1005Metric,Panasonic,ERJ-2RKF4701X,Digikey,P4.70KLCT-ND,
50,1,R4,649R,R_0402_1005Metric,Panasonic,ERA-2AEB6490X,Digikey,P649DCCT-ND,
51,1,SW1,SW_DPDT_x2,TL2230,E-Switch,TL2230OAF140,Digikey,EG6032-ND,
52,1,SW2,SW_Push,SW_PUSH_6mm_H5mm,TE Connectivity,1825910-7,Digikey,450-1804-ND,
53,1,U6,74AHC1G08,SOT-353_SC-70-5,TI,SN74AHC1G08DCKR,Digikey,296-8743-1-ND,
54,1,U22,74LVC1G34,SOT-23-5,TI,SN74LVC1G34DBVR,Digikey,296-17893-1-ND,
55,1,U21,ARJ11C-MBSAS-A-BA-7MU2,ARJ11C-MBSAS-A-BA-7MU2,Abracon,ARJ11C-MBSAS-A-BA-7MU2,Digikey,ARJ11C-MBSAS-A-BA-7MU2-ND,
56,1,U3,CY7C65642-28LTXC,QFN-28-1EP_5x5mm_P0.5mm_EP3.35x3.35mm,Cypress,CY7C65642-28LTXC,Digikey,428-3149-ND,
57,2,U9 U11,EN5322QI,Converter_DCDC_Intel_QFN-24_4x6mm_P0.65mm_ThermalVias,Intel,EN5322QI,Digikey,544-2849-1-ND,
58,1,U4,HD3SS3202,TI_R_PUQFN_N16,TI,HD3SS3202IRSVT,Digikey,296-52295-1-ND,
59,1,U25,ICM42688,LGA-14_3x2.5mm_P0.5mm_LayoutBorder3x4y,TDK Invensense,ICM-42688-P,Digikey,1428-ICM-42688-PCT-ND,
60,1,U1,Jetson_Nano,TE_2309413-1,TE Connectivity,2309413-1,Digikey,A126764CT-ND,
61,1,U5,LM3526-L,SO-8_3.9x4.9mm_P1.27mm,TI,LM3526MX-L/NOPB,Digikey,LM3526MX-L/NOPBCT-ND,
62,1,U20,LPC55S66JBD100,QFP-100-1EP_3.21x3.21mm_14x14_Pitch0.5mm,NXP,LPC55S69JBD100K,Digikey,568-15313-ND,
63,1,U24,SN74AUP1T34DCK,SOT-353_SC-70-5,TI,SN74AUP1T34DCKR,Digikey,296-34900-1-ND,
64,1,U23,SN74LVC1G04,SOT-353_SC-70-5,TI,SN74LVC1G04DCKR,Digikey,296-11600-1-ND,
65,2,U12 U19,SN74LVC1T45DBV,SOT-23-6,TI,SN74LVC1T45DBVR,Digikey,296-16843-1-ND,
66,1,U2,STUSB4500,QFN-24-1EP_4x4mm_P0.5mm_EP2.7x2.7mm,ST,STUSB4500LQTR,Digikey,497-STUSB4500LQCT-ND,
67,2,U8 U10,TPS2121,Texas_VQFN-HR-12_2x2.5_Pitch0.5mm,TI,TPS2121RUXR,Digikey,296-53410-1-ND,
68,1,U7,TPSM53604,TI_B3QFN,TI,TPSM53604RDAR,Digikey,296-TPSM53604RDARCT-ND,
69,1,U26,TVS2200DRV,WSON-6-1EP_2x2mm_P0.65mm_EP1x1.6mm,TI,TVS2200DRVR,Mouser,595-TVS2200DRVR,
70,1,U18,USBA_DUAL,USBA_DUAL_HOR,Amphenol,72309-8034BLF,Digikey,609-1040-ND,
71,1,Y1,12MHz,Crystal_SMD_5032-2Pin_5.0x3.2mm,Kyocera,CX5032GB12000H0HPQZ1,Digikey,1253-1375-1-ND,
72,1,Y2,16MHz,Crystal_SMD_5032-2Pin_5.0x3.2mm,Kyocera,CX5032GB16000H0PESZZ,Digikey,478-4362-1-ND,





Component Groups:,72
Component Count:,181
Fitted Components:,181
Number of PCBs:,1
Total components:,181
Schematic Version:,
Schematic Date:,
PCB Variant:,['default']
BoM Date:,Mon Jun 22 18:16:15 2020
Schematic Source:,ovc4.kicad_sch
KiCad Version:,Eeschema 5.99.0-unknown-ad69e44~101~ubuntu18.04.1

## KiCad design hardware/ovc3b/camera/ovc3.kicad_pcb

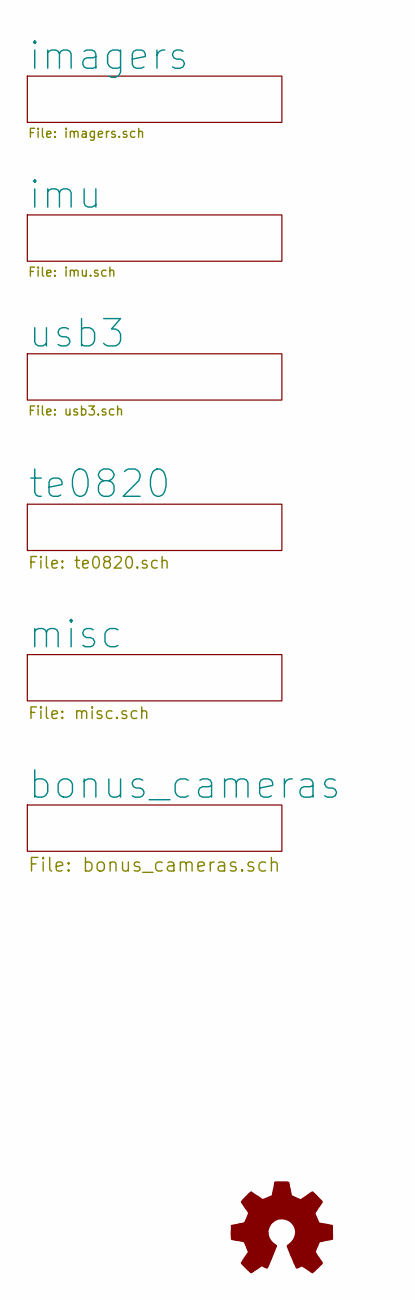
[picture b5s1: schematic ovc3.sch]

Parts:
LOGO1: Logo_Open_Hardware_Small; OSHW-Symbol_6.7x6mm_SilkScreen; MPN DNP

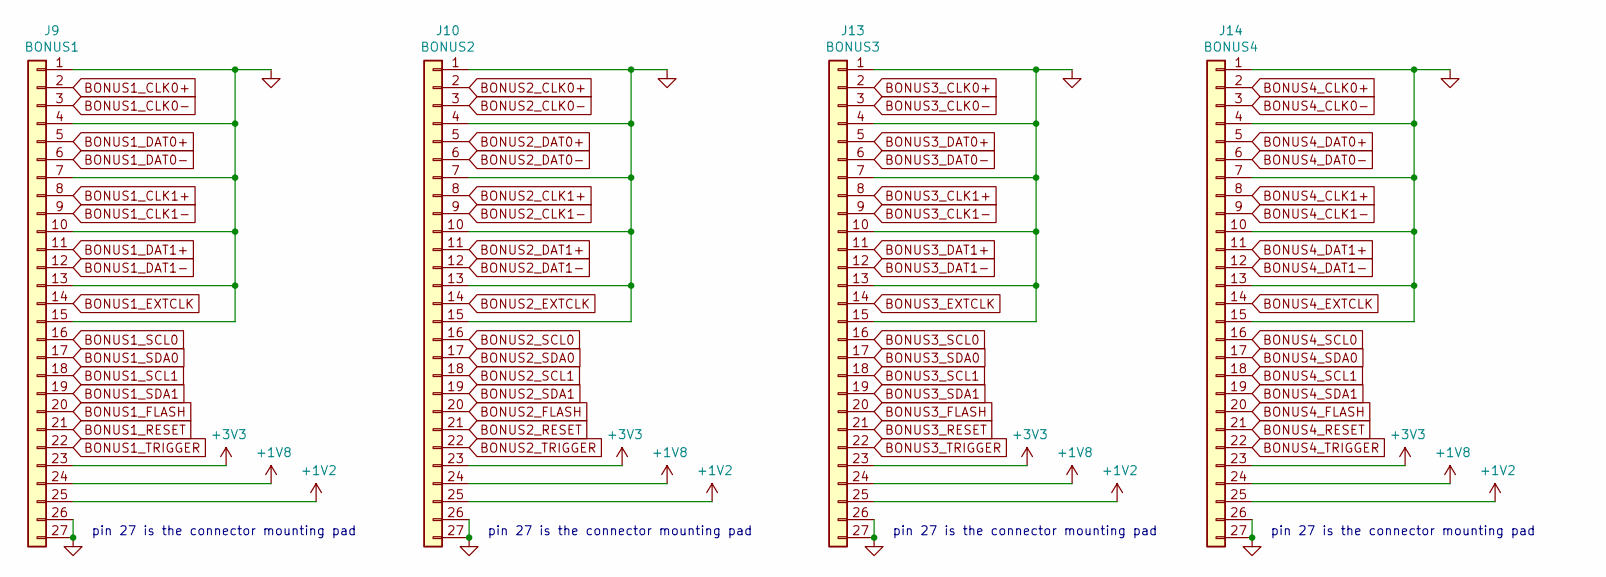
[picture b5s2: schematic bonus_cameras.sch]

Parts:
J9: BONUS1; MOLEX_505110_2691; MPN 5051102691
J10: BONUS2; MOLEX_505110_2691; MPN 5051102691
J13: BONUS3; MOLEX_505110_2691; MPN 5051102691
J14: BONUS4; MOLEX_505110_2691; MPN 5051102691

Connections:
+1V2: J9.25, J10.25, J13.25, J14.25; also elsewhere on the board
+1V8: J9.24, J10.24, J13.24, J14.24; also elsewhere on the board
BONUS1_CLK0+: J9.2; also elsewhere on the board
BONUS1_CLK0-: J9.3; also elsewhere on the board
BONUS1_CLK1+: J9.8; also elsewhere on the board
BONUS1_CLK1-: J9.9; also elsewhere on the board
BONUS1_DAT0+: J9.5; also elsewhere on the board
BONUS1_DAT0-: J9.6; also elsewhere on the board
BONUS1_DAT1+: J9.11; also elsewhere on the board
BONUS1_DAT1-: J9.12; also elsewhere on the board
BONUS1_EXTCLK: J9.14; also elsewhere on the board
BONUS1_FLASH: J9.20; also elsewhere on the board
BONUS1_RESET: J9.21; also elsewhere on the board
BONUS1_SCL0: J9.16; also elsewhere on the board
BONUS1_SCL1: J9.18; also elsewhere on the board
BONUS1_SDA0: J9.17; also elsewhere on the board
BONUS1_SDA1: J9.19; also elsewhere on the board
BONUS1_TRIGGER: J9.22; also elsewhere on the board
BONUS2_CLK0+: J10.2; also elsewhere on the board
BONUS2_CLK0-: J10.3; also elsewhere on the board
BONUS2_CLK1+: J10.8; also elsewhere on the board
BONUS2_CLK1-: J10.9; also elsewhere on the board
BONUS2_DAT0+: J10.5; also elsewhere on the board
BONUS2_DAT0-: J10.6; also elsewhere on the board
BONUS2_DAT1+: J10.11; also elsewhere on the board
BONUS2_DAT1-: J10.12; also elsewhere on the board
BONUS2_EXTCLK: J10.14; also elsewhere on the board
BONUS2_FLASH: J10.20; also elsewhere on the board
BONUS2_RESET: J10.21; also elsewhere on the board
BONUS2_SCL0: J10.16; also elsewhere on the board
BONUS2_SCL1: J10.18; also elsewhere on the board
BONUS2_SDA0: J10.17; also elsewhere on the board
BONUS2_SDA1: J10.19; also elsewhere on the board
BONUS2_TRIGGER: J10.22; also elsewhere on the board
BONUS3_CLK0+: J13.2; also elsewhere on the board
BONUS3_CLK0-: J13.3; also elsewhere on the board
BONUS3_CLK1+: J13.8; also elsewhere on the board
BONUS3_CLK1-: J13.9; also elsewhere on the board
BONUS3_DAT0+: J13.5; also elsewhere on the board
BONUS3_DAT0-: J13.6; also elsewhere on the board
BONUS3_DAT1+: J13.11; also elsewhere on the board
BONUS3_DAT1-: J13.12; also elsewhere on the board
BONUS3_EXTCLK: J13.14; also elsewhere on the board
BONUS3_FLASH: J13.20; also elsewhere on the board
BONUS3_RESET: J13.21; also elsewhere on the board
BONUS3_SCL0: J13.16; also elsewhere on the board
BONUS3_SCL1: J13.18; also elsewhere on the board
BONUS3_SDA0: J13.17; also elsewhere on the board
BONUS3_SDA1: J13.19; also elsewhere on the board
BONUS3_TRIGGER: J13.22; also elsewhere on the board
BONUS4_CLK0+: J14.2; also elsewhere on the board
BONUS4_CLK0-: J14.3; also elsewhere on the board
BONUS4_CLK1+: J14.8; also elsewhere on the board
BONUS4_CLK1-: J14.9; also elsewhere on the board
BONUS4_DAT0+: J14.5; also elsewhere on the board
BONUS4_DAT0-: J14.6; also elsewhere on the board
BONUS4_DAT1+: J14.11; also elsewhere on the board
BONUS4_DAT1-: J14.12; also elsewhere on the board
BONUS4_EXTCLK: J14.14; also elsewhere on the board
BONUS4_FLASH: J14.20; also elsewhere on the board
BONUS4_RESET: J14.21; also elsewhere on the board
BONUS4_SCL0: J14.16; also elsewhere on the board
BONUS4_SCL1: J14.18; also elsewhere on the board
BONUS4_SDA0: J14.17; also elsewhere on the board
BONUS4_SDA1: J14.19; also elsewhere on the board
BONUS4_TRIGGER: J14.22; also elsewhere on the board
GND: J9.1, J9.4, J9.7, J9.10, J9.13, J9.15, J9.26, J9.27, J10.1, J10.4, J10.7, J10.10, J10.13, J10.15, J10.26, J10.27, J13.1, J13.4, J13.7, J13.10, J13.13, J13.15, J13.26, J13.27, J14.1, J14.4, J14.7, J14.10, J14.13, J14.15, J14.26, J14.27; also elsewhere on the board

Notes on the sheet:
pin 27 is the connector mounting pad
